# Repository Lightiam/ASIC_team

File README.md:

# ASIC_team

Consolidating codes

This repository is intended to hold consolidated code and resources for the ASIC team.

## Authors & Contributors

- ** RTL and Digital Designer:** Talha Alam
- ** Architect, Co-Designer:** Founder, CEO-  Bola Olatunji

## Getting started

- Clone the repository: `git clone git@github.com:Lightiam/ASIC_team.git`
- Create a branch for your work: `git checkout -b feat/your-feature`
- Commit and open a pull request against `main`.

## Contributing

Please follow a lightweight workflow:
- Use feature branches (branch names like `feat/...`, `fix/...`, `chore/...`).
- Open pull requests and request a review.
- Keep commits small and descriptive.

## License

This repository is released under CC0 1.0 Universal. See the LICENSE file.

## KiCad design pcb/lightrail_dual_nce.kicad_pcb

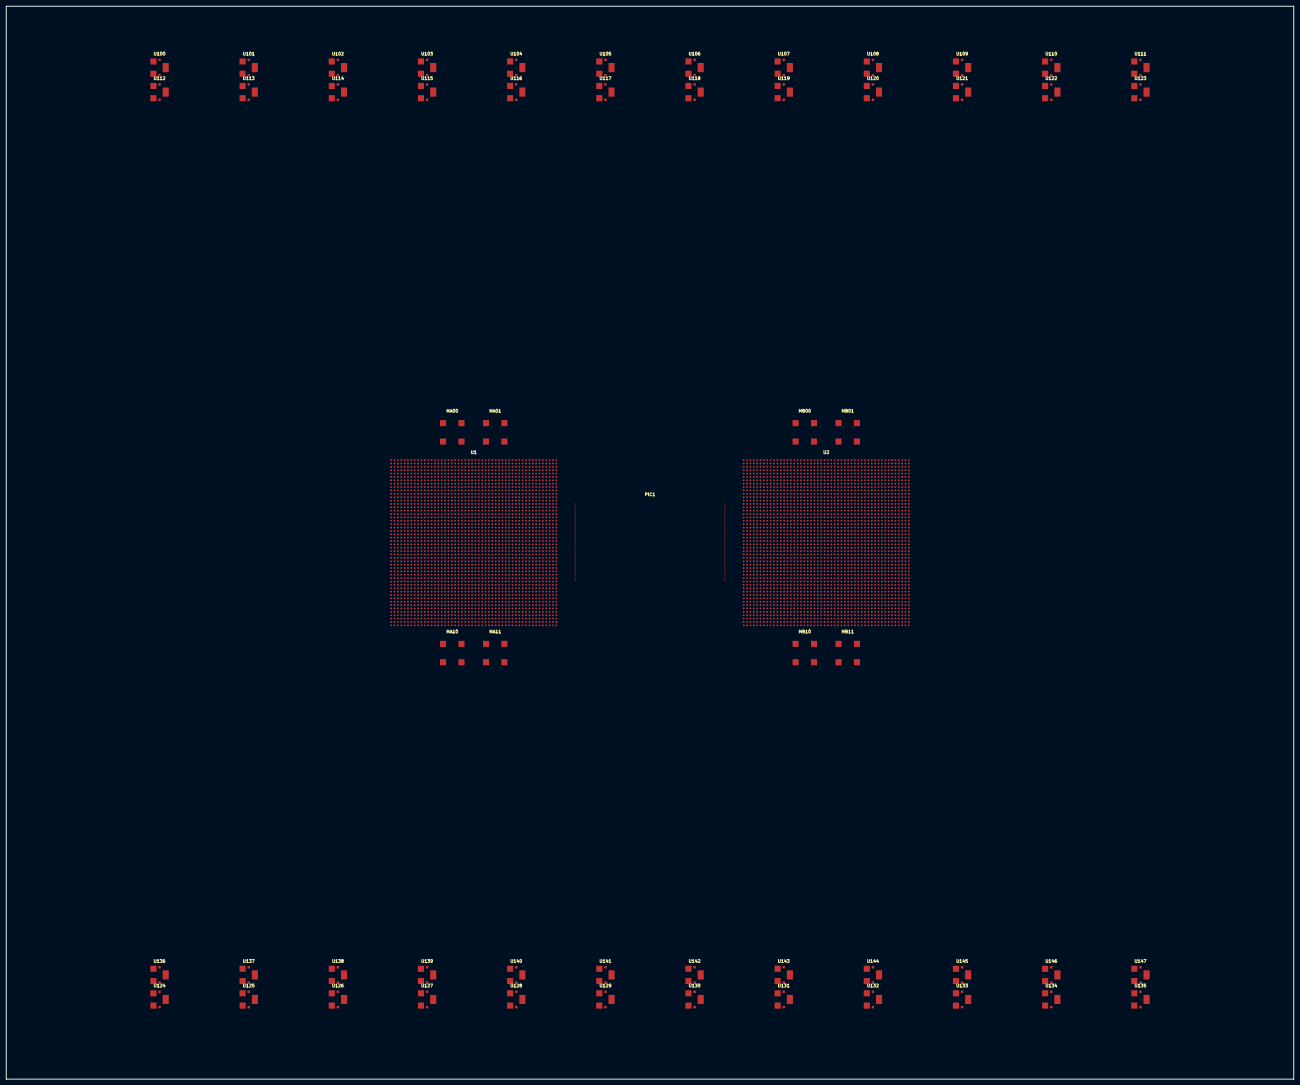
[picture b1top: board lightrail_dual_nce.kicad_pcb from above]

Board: 32 copper layers, 420.0 x 350.0 mm, 59 parts (0 on the bottom side), 131 nets, no tracks yet.

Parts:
MA00, MA01, MA10, MA11: HBM4-12Hi
MB00, MB01, MB10, MB11: HBM4-12Hi
PIC1: TFLN-BRIDGE-3T2
U1, U2: NCE-BGA2500
U100, U101, U102, U103, U104, U105, U106, U107, U108, U109, U110, U111, U112, U113, U114, U115, U116, U117, U118, U119, U120, U121, U122, U123, U124, U125, U126, U127, U128, U129, U130, U131, U132, U133, U134, U135, U136, U137, U138, U139, U140, U141, U142, U143, U144, U145, U146, U147: DrMOS

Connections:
GND: MA00.GND, MA00.VSSQ, MA01.GND, MA01.VSSQ, MA10.GND, MA10.VSSQ, MA11.GND, MA11.VSSQ, MB00.GND, MB00.VSSQ, MB01.GND, MB01.VSSQ, MB10.GND, MB10.VSSQ, MB11.GND, MB11.VSSQ, U1.AA4, U1.AA6, U1.AA8, U1.AA10, U1.AA12, U1.AA14, U1.AA16, U1.AA18, U1.AA20, U1.AA22, U1.AA24, U1.AA26, U1.AA28, U1.AA30, U1.AA32, U1.AA34, U1.AA36, U1.AA38, U1.AA40, U1.AA42, U1.AA44, U1.AA46, U1.AB3, U1.AB5, U1.AB7, U1.AB9, U1.AB11, U1.AB13, U1.AB15, U1.AB17, U1.AB19, U1.AB21, U1.AB23, U1.AB25, U1.AB27, U1.AB29, U1.AB31, U1.AB33, U1.AB35, U1.AB37, U1.AB39, U1.AB41, U1.AB43, U1.AB45, U1.AB47, U1.AC4, U1.AC6, U1.AC8, U1.AC10, U1.AC12, U1.AC14, U1.AC16, U1.AC18, U1.AC20, U1.AC22, U1.AC24, U1.AC26, U1.AC28, U1.AC30, U1.AC32, U1.AC34, U1.AC36, U1.AC38, U1.AC40, U1.AC42, U1.AC44, U1.AC46, U1.AD3, U1.AD5, U1.AD7, U1.AD9, U1.AD11, U1.AD13, U1.AD15, U1.AD17, U1.AD19, U1.AD21, U1.AD23, U1.AD25, U1.AD27, U1.AD29, U1.AD31, U1.AD33, U1.AD35, U1.AD37, U1.AD39, U1.AD41, U1.AD43, U1.AD45, U1.AD47, U1.AE4, U1.AE6, U1.AE8, U1.AE10, U1.AE12, U1.AE14, U1.AE16, U1.AE18, U1.AE20, U1.AE22, U1.AE24, U1.AE26, U1.AE28, U1.AE30, U1.AE32, U1.AE34, U1.AE36, U1.AE38, U1.AE40, U1.AE42, U1.AE44, U1.AE46, U1.AF3, U1.AF5, U1.AF7, U1.AF9, U1.AF11, U1.AF13, U1.AF15, U1.AF17, U1.AF19, U1.AF21, U1.AF23, U1.AF25, U1.AF27, U1.AF29, U1.AF31, U1.AF33, U1.AF35, U1.AF37, U1.AF39, U1.AF41, U1.AF43, U1.AF45, U1.AF47, U1.AG4, U1.AG6, U1.AG8, U1.AG10, U1.AG12, U1.AG14, U1.AG16, U1.AG18, U1.AG20, U1.AG22, U1.AG24, U1.AG26, U1.AG28, U1.AG30, U1.AG32, U1.AG34, U1.AG36, U1.AG38, U1.AG40, U1.AG42, U1.AG44, U1.AG46, U1.AH3, U1.AH5, U1.AH7, U1.AH9, U1.AH11, U1.AH13, U1.AH15, U1.AH17, U1.AH19, U1.AH21, U1.AH23, U1.AH25, U1.AH27, U1.AH29, U1.AH31, U1.AH33, U1.AH35, U1.AH37, U1.AH39, U1.AH41, U1.AH43, U1.AH45, U1.AH47, U1.AJ4, U1.AJ6, U1.AJ8, U1.AJ10, U1.AJ12, U1.AJ14, U1.AJ16, U1.AJ18, U1.AJ20, U1.AJ22, U1.AJ24, U1.AJ26, U1.AJ28, U1.AJ30, U1.AJ32, U1.AJ34, U1.AJ36, U1.AJ38, U1.AJ40, U1.AJ42, U1.AJ44, U1.AJ46, U1.AK3, U1.AK5, U1.AK7, U1.AK9, U1.AK11, U1.AK13, U1.AK15, U1.AK17, U1.AK19, U1.AK21, U1.AK23, U1.AK25, U1.AK27, U1.AK29, U1.AK31, U1.AK33, U1.AK35, U1.AK37, U1.AK39, U1.AK41, U1.AK43, U1.AK45, U1.AK47, U1.AL4, U1.AL6, U1.AL8, U1.AL10, U1.AL12, U1.AL14, U1.AL16, U1.AL18, U1.AL20, U1.AL22, U1.AL24, U1.AL26, U1.AL28, U1.AL30, U1.AL32, U1.AL34, U1.AL36, U1.AL38, U1.AL40, U1.AL42, U1.AL44, U1.AL46, U1.AM3, U1.AM5, U1.AM7, U1.AM9, U1.AM11, U1.AM13, U1.AM15, U1.AM17, U1.AM19, U1.AM21, U1.AM23, U1.AM25, U1.AM27, U1.AM29, U1.AM31, U1.AM33, U1.AM35, U1.AM37, U1.AM39, U1.AM41, U1.AM43, U1.AM45, U1.AM47, U1.AN4, U1.AN6, U1.AN8, U1.AN10, U1.AN12, U1.AN14, U1.AN16, U1.AN18, U1.AN20, U1.AN22, U1.AN24, U1.AN26, U1.AN28, U1.AN30, U1.AN32, U1.AN34, U1.AN36, U1.AN38, U1.AN40, U1.AN42, U1.AN44, U1.AN46, U1.AP3, U1.AP5, U1.AP7, U1.AP9, U1.AP11, U1.AP13, U1.AP15, U1.AP17, U1.AP19, U1.AP21, U1.AP23, U1.AP25, U1.AP27, U1.AP29, U1.AP31, U1.AP33, U1.AP35, U1.AP37, U1.AP39, U1.AP41, U1.AP43, U1.AP45, U1.AP47, U1.AR4, U1.AR6, U1.AR8, U1.AR10, U1.AR12, U1.AR14, U1.AR16, U1.AR18, U1.AR20, U1.AR22, U1.AR24, U1.AR26, U1.AR28, U1.AR30, U1.AR32, U1.AR34, U1.AR36, U1.AR38, U1.AR40, U1.AR42, U1.AR44, U1.AR46, U1.AT3, U1.AT5, U1.AT7, U1.AT9, U1.AT11, U1.AT13, U1.AT15, U1.AT17, U1.AT19, U1.AT21, U1.AT23, U1.AT25, U1.AT27, U1.AT29, U1.AT31, U1.AT33, U1.AT35, U1.AT37, U1.AT39, U1.AT41, U1.AT43, U1.AT45, U1.AT47, U1.AU4, U1.AU6, U1.AU8, U1.AU10, U1.AU12, U1.AU14, U1.AU16, U1.AU18, U1.AU20, U1.AU22, U1.AU24, U1.AU26, U1.AU28, U1.AU30, U1.AU32, U1.AU34, U1.AU36, U1.AU38, U1.AU40, U1.AU42, U1.AU44, U1.AU46, U1.AU48, U1.AV3, U1.AV5, U1.AV7, U1.AV9, U1.AV11, U1.AV13, U1.AV15, U1.AV17, U1.AV19, U1.AV21, U1.AV23, U1.AV25, U1.AV27, U1.AV29, U1.AV31, U1.AV33, U1.AV35, U1.AV37, U1.AV39, U1.AV41, U1.AV43, U1.AV45, U1.AV47, U1.AW4, U1.AW6, U1.AW8, U1.AW10, U1.AW12, U1.AW14, U1.AW16, U1.AW18, U1.AW20, U1.AW22, U1.AW24, U1.AW26, U1.AW28, U1.AW30, U1.AW32, U1.AW34, U1.AW36, U1.AW38, U1.AW40, U1.AW42, U1.AW44, U1.AW46, U1.AW48, U1.AY3, U1.AY5, U1.AY7, U1.AY9, U1.AY11, U1.AY13, U1.AY15, U1.AY17, U1.AY19, U1.AY21, U1.AY23, U1.AY25, U1.AY27, U1.AY29, U1.AY31, U1.AY33, U1.AY35, U1.AY37, U1.AY39, U1.AY41, U1.AY43, U1.AY45, U1.AY47, U1.BA4, U1.BA6, U1.BA8, U1.BA10, U1.BA12, U1.BA14, U1.BA16, U1.BA18, U1.BA20, U1.BA22, U1.BA24, U1.BA26, U1.BA28, U1.BA30, U1.BA32, U1.BA34, U1.BA36, U1.BA38, U1.BA40, U1.BA42, U1.BA44, U1.BA46, U1.BA48, U1.BB3, U1.BB5, U1.BB7, U1.BB9, U1.BB11, U1.BB13, U1.BB15, U1.BB17, U1.BB19, U1.BB21, U1.BB23, U1.BB25, U1.BB27, U1.BB29, U1.BB31, U1.BB33, U1.BB35, U1.BB37, U1.BB39, U1.BB41, U1.BB43, U1.BB45, U1.BB47, U1.BC4, U1.BC6, U1.BC8, U1.BC10, U1.BC12, U1.BC14, U1.BC16, U1.BC18, U1.BC20, U1.BC22, U1.BC24, U1.BC26, U1.BC28, U1.BC30, U1.BC32, U1.BC34, U1.BC36, U1.BC38, U1.BC40, U1.BC42, U1.BC44, U1.BC46, U1.BC48, U1.BD3, U1.BD5, U1.BD7, U1.BD9, U1.BD11, U1.BD13, U1.BD15, U1.BD17, U1.BD19, U1.BD21, U1.BD23, U1.BD25, U1.BD27, U1.BD29, U1.BD31, U1.BD33, U1.BD35, U1.BD37, U1.BD39, U1.BD41, U1.BD43, U1.BD45, U1.BD47, U1.BE4, U1.BE6, U1.BE8, U1.BE10, U1.BE12, U1.BE14, U1.BE16, U1.BE18, U1.BE20, U1.BE22, U1.BE24, U1.BE26, U1.BE28, U1.BE30, U1.BE32, U1.BE34, U1.BE36, U1.BE38, U1.BE40, U1.BE42, U1.BE44, U1.BE46, U1.BE48, U1.BF3, U1.BF5, U1.BF7, U1.BF9, U1.BF11, U1.BF13, U1.BF15, U1.BF17, U1.BF19, U1.BF21, U1.BF23, U1.BF25, U1.BF27, U1.BF29, U1.BF31, U1.BF33, U1.BF35, U1.BF37, U1.BF39, U1.BF41, U1.BF43, U1.BF45, U1.BF47, U1.BG4, U1.BG6, U1.BG8, U1.BG10, U1.BG12, U1.BG14, U1.BG16, U1.BG18, U1.BG20, U1.BG22, U1.BG24, U1.BG26, U1.BG28, U1.BG30, U1.BG32, U1.BG34, U1.BG36, U1.BG38, U1.BG40, U1.BG42, U1.BG44, U1.BG46, U1.BG48, U1.BH3, U1.BH5, U1.BH7, U1.BH9, U1.BH11, U1.BH13, U1.BH15, U1.BH17, U1.BH19, U1.BH21, U1.BH23, U1.BH25, U1.BH27, U1.BH29, U1.BH31, U1.BH33, U1.BH35, U1.BH37, U1.BH39, U1.BH41, U1.BH43, U1.BH45, U1.BH47, U1.C4, U1.C6, U1.C8, U1.C10, U1.C12, U1.C14, U1.C16, U1.C18, U1.C20, U1.C22, U1.C24, U1.C26, U1.C28, U1.C30, U1.C32, U1.C34, U1.C36, U1.C38, U1.C40, U1.C42, U1.C44, U1.C46, U1.C48, U1.D3, U1.D5, U1.D7, U1.D9, U1.D11, U1.D13, U1.D15, U1.D17, U1.D19, U1.D21, U1.D23, U1.D25, U1.D27, U1.D29, U1.D31, U1.D33, U1.D35, U1.D37, U1.D39, U1.D41, U1.D43, U1.D45, U1.D47, U1.E4, U1.E6, U1.E8, U1.E10, U1.E12, U1.E14, U1.E16, U1.E18, U1.E20, U1.E22, U1.E24, U1.E26, U1.E28, U1.E30, U1.E32, U1.E34, U1.E36, U1.E38, U1.E40, U1.E42, U1.E44, U1.E46, U1.F3, U1.F5, U1.F7, U1.F9, U1.F11, U1.F13, U1.F15, U1.F17, U1.F19, U1.F21, U1.F23, U1.F25, U1.F27, U1.F29, U1.F31, U1.F33, U1.F35, U1.F37, U1.F39, U1.F41, U1.F43, U1.F45, U1.F47, U1.G4, U1.G6, U1.G8, U1.G10, U1.G12, U1.G14, U1.G16, U1.G18, U1.G20, U1.G22, U1.G24, U1.G26, U1.G28, U1.G30, U1.G32, U1.G34, U1.G36, U1.G38, U1.G40, U1.G42, U1.G44, U1.G46, U1.H3, U1.H5, U1.H7, U1.H9, U1.H11, U1.H13, U1.H15, U1.H17, U1.H19, U1.H21, U1.H23, U1.H25, U1.H27, U1.H29, U1.H31, U1.H33, U1.H35, U1.H37, U1.H39, U1.H41, U1.H43, U1.H45, U1.H47, U1.J4, U1.J6, U1.J8, U1.J10, U1.J12, U1.J14, U1.J16, U1.J18, U1.J20, U1.J22, U1.J24, U1.J26, U1.J28, U1.J30, U1.J32, U1.J34, U1.J36, U1.J38, U1.J40, U1.J42, U1.J44, U1.J46, U1.K3, U1.K5, U1.K7, U1.K9, U1.K11, U1.K13, U1.K15, U1.K17, U1.K19, U1.K21, U1.K23, U1.K25, U1.K27, U1.K29, U1.K31, U1.K33, U1.K35, U1.K37, U1.K39, U1.K41, U1.K43, U1.K45, U1.K47, U1.L4, U1.L6, U1.L8, U1.L10, U1.L12, U1.L14, U1.L16, U1.L18, U1.L20, U1.L22, U1.L24, U1.L26, U1.L28, U1.L30, U1.L32, U1.L34, U1.L36, U1.L38, U1.L40, U1.L42, U1.L44, U1.L46, U1.M3, U1.M5, U1.M7, U1.M9, U1.M11, U1.M13, U1.M15, U1.M17, U1.M19, U1.M21, U1.M23, U1.M25, U1.M27, U1.M29, U1.M31, U1.M33, U1.M35, U1.M37, U1.M39, U1.M41, U1.M43, U1.M45, U1.M47, U1.N4, U1.N6, U1.N8, U1.N10, U1.N12, U1.N14, U1.N16, U1.N18, U1.N20, U1.N22, U1.N24, U1.N26, U1.N28, U1.N30, U1.N32, U1.N34, U1.N36, U1.N38, U1.N40, U1.N42, U1.N44, U1.N46, U1.P3, U1.P5, U1.P7, U1.P9, U1.P11, U1.P13, U1.P15, U1.P17, U1.P19, U1.P21, U1.P23, U1.P25, U1.P27, U1.P29, U1.P31, U1.P33, U1.P35, U1.P37, U1.P39, U1.P41, U1.P43, U1.P45, U1.P47, U1.R4, U1.R6, U1.R8, U1.R10, U1.R12, U1.R14, U1.R16, U1.R18, U1.R20, U1.R22, U1.R24, U1.R26, U1.R28, U1.R30, U1.R32, U1.R34, U1.R36, U1.R38, U1.R40, U1.R42, U1.R44, U1.R46, U1.T3, U1.T5, U1.T7, U1.T9, U1.T11, U1.T13, U1.T15, U1.T17, U1.T19, U1.T21, U1.T23, U1.T25, U1.T27, U1.T29, U1.T31, U1.T33, U1.T35, U1.T37, U1.T39, U1.T41, U1.T43, U1.T45, U1.T47, U1.U4, U1.U6, U1.U8, U1.U10, U1.U12, U1.U14, U1.U16, U1.U18, U1.U20, U1.U22, U1.U24, U1.U26, U1.U28, U1.U30, U1.U32, U1.U34, U1.U36, U1.U38, U1.U40, U1.U42, U1.U44, U1.U46, U1.V3, U1.V5, U1.V7, U1.V9, U1.V11, U1.V13, U1.V15, U1.V17, U1.V19, U1.V21, U1.V23, U1.V25, U1.V27, U1.V29, U1.V31, U1.V33, U1.V35, U1.V37, U1.V39, U1.V41, U1.V43, U1.V45, U1.V47, U1.W4, U1.W6, U1.W8, U1.W10, U1.W12, U1.W14, U1.W16, U1.W18, U1.W20, U1.W22, U1.W24, U1.W26, U1.W28, U1.W30, U1.W32, U1.W34, U1.W36, U1.W38, U1.W40, U1.W42, U1.W44, U1.W46, U1.Y3, U1.Y5, U1.Y7, U1.Y9, U1.Y11, U1.Y13, U1.Y15, U1.Y17, U1.Y19, U1.Y21, U1.Y23, U1.Y25, U1.Y27, U1.Y29, U1.Y31, U1.Y33, U1.Y35, U1.Y37, U1.Y39, U1.Y41, U1.Y43, U1.Y45, U1.Y47, U2.AA4, U2.AA6, U2.AA8, U2.AA10, U2.AA12, U2.AA14, U2.AA16, U2.AA18, U2.AA20, U2.AA22, U2.AA24, U2.AA26, U2.AA28, U2.AA30, U2.AA32, U2.AA34, U2.AA36, U2.AA38, U2.AA40, U2.AA42, U2.AA44, U2.AA46, U2.AA48, U2.AB5, U2.AB7, U2.AB9, U2.AB11, U2.AB13, U2.AB15, U2.AB17, U2.AB19, U2.AB21, U2.AB23, U2.AB25, U2.AB27, U2.AB29, U2.AB31, U2.AB33, U2.AB35, U2.AB37, U2.AB39, U2.AB41, U2.AB43, U2.AB45, U2.AB47, U2.AC4, U2.AC6, U2.AC8, U2.AC10, U2.AC12, U2.AC14, U2.AC16, U2.AC18, U2.AC20, U2.AC22, U2.AC24, U2.AC26, U2.AC28, U2.AC30, U2.AC32, U2.AC34, U2.AC36, U2.AC38, U2.AC40, U2.AC42, U2.AC44, U2.AC46, U2.AC48, U2.AD5, U2.AD7, U2.AD9, U2.AD11, U2.AD13, U2.AD15, U2.AD17, U2.AD19, U2.AD21, U2.AD23, U2.AD25, U2.AD27, U2.AD29, U2.AD31, U2.AD33, U2.AD35, U2.AD37, U2.AD39, U2.AD41, U2.AD43, U2.AD45, U2.AD47, U2.AE4, U2.AE6, U2.AE8, U2.AE10, U2.AE12, U2.AE14, U2.AE16, U2.AE18, U2.AE20, U2.AE22, U2.AE24, U2.AE26, U2.AE28, U2.AE30, U2.AE32, U2.AE34, U2.AE36, U2.AE38, U2.AE40, U2.AE42, U2.AE44, U2.AE46, U2.AE48, U2.AF5, U2.AF7, U2.AF9, U2.AF11, U2.AF13, U2.AF15, U2.AF17, U2.AF19, U2.AF21, U2.AF23, U2.AF25, U2.AF27, U2.AF29, U2.AF31, U2.AF33, U2.AF35, U2.AF37, U2.AF39, U2.AF41, U2.AF43, U2.AF45, U2.AF47, U2.AG4, U2.AG6, U2.AG8, U2.AG10, U2.AG12, U2.AG14, U2.AG16, U2.AG18, U2.AG20, U2.AG22, U2.AG24, U2.AG26, U2.AG28, U2.AG30, U2.AG32, U2.AG34, U2.AG36, U2.AG38, U2.AG40, U2.AG42, U2.AG44, U2.AG46, U2.AG48, U2.AH5, U2.AH7, U2.AH9, U2.AH11, U2.AH13, U2.AH15, U2.AH17, U2.AH19, U2.AH21, U2.AH23, U2.AH25, U2.AH27, U2.AH29, U2.AH31, U2.AH33, U2.AH35, U2.AH37, U2.AH39, U2.AH41, U2.AH43, U2.AH45, U2.AH47, U2.AJ4, U2.AJ6, U2.AJ8, U2.AJ10, U2.AJ12, U2.AJ14, U2.AJ16, U2.AJ18, U2.AJ20, U2.AJ22, U2.AJ24, U2.AJ26, U2.AJ28, U2.AJ30, U2.AJ32, U2.AJ34, U2.AJ36, U2.AJ38, U2.AJ40, U2.AJ42, U2.AJ44, U2.AJ46, U2.AJ48, U2.AK5, U2.AK7, U2.AK9, U2.AK11, U2.AK13, U2.AK15, U2.AK17, U2.AK19, U2.AK21, U2.AK23, U2.AK25, U2.AK27, U2.AK29, U2.AK31, U2.AK33, U2.AK35, U2.AK37, U2.AK39, U2.AK41, U2.AK43, U2.AK45, U2.AK47, U2.AL4, U2.AL6, U2.AL8, U2.AL10, U2.AL12, U2.AL14, U2.AL16, U2.AL18, U2.AL20, U2.AL22, U2.AL24, U2.AL26, U2.AL28, U2.AL30, U2.AL32, U2.AL34, U2.AL36, U2.AL38, U2.AL40, U2.AL42, U2.AL44, U2.AL46, U2.AL48, U2.AM5, U2.AM7, U2.AM9, U2.AM11, U2.AM13, U2.AM15, U2.AM17, U2.AM19, U2.AM21, U2.AM23, U2.AM25, U2.AM27, U2.AM29, U2.AM31, U2.AM33, U2.AM35, U2.AM37, U2.AM39, U2.AM41, U2.AM43, U2.AM45, U2.AM47, U2.AN4, U2.AN6, U2.AN8, U2.AN10, U2.AN12, U2.AN14, U2.AN16, U2.AN18, U2.AN20, U2.AN22, U2.AN24, U2.AN26, U2.AN28, U2.AN30, U2.AN32, U2.AN34, U2.AN36, U2.AN38, U2.AN40, U2.AN42, U2.AN44, U2.AN46, U2.AN48, U2.AP5, U2.AP7, U2.AP9, U2.AP11, U2.AP13, U2.AP15, U2.AP17, U2.AP19, U2.AP21, U2.AP23, U2.AP25, U2.AP27, U2.AP29, U2.AP31, U2.AP33, U2.AP35, U2.AP37, U2.AP39, U2.AP41, U2.AP43, U2.AP45, U2.AP47, U2.AR4, U2.AR6, U2.AR8, U2.AR10, U2.AR12, U2.AR14, U2.AR16, U2.AR18, U2.AR20, U2.AR22, U2.AR24, U2.AR26, U2.AR28, U2.AR30, U2.AR32, U2.AR34, U2.AR36, U2.AR38, U2.AR40, U2.AR42, U2.AR44, U2.AR46, U2.AR48, U2.AT5, U2.AT7, U2.AT9, U2.AT11, U2.AT13, U2.AT15, U2.AT17, U2.AT19, U2.AT21, U2.AT23, U2.AT25, U2.AT27, U2.AT29, U2.AT31, U2.AT33, U2.AT35, U2.AT37, U2.AT39, U2.AT41, U2.AT43, U2.AT45, U2.AT47, U2.AU4, U2.AU6, U2.AU8, U2.AU10, U2.AU12, U2.AU14, U2.AU16, U2.AU18, U2.AU20, U2.AU22, U2.AU24, U2.AU26, U2.AU28, U2.AU30, U2.AU32, U2.AU34, U2.AU36, U2.AU38, U2.AU40, U2.AU42, U2.AU44, U2.AU46, U2.AU48, U2.AV3, U2.AV5, U2.AV7, U2.AV9, U2.AV11, U2.AV13, U2.AV15, U2.AV17, U2.AV19, U2.AV21, U2.AV23, U2.AV25, U2.AV27, U2.AV29, U2.AV31, U2.AV33, U2.AV35, U2.AV37, U2.AV39, U2.AV41, U2.AV43, U2.AV45, U2.AV47, U2.AW4, U2.AW6, U2.AW8, U2.AW10, U2.AW12, U2.AW14, U2.AW16, U2.AW18, U2.AW20, U2.AW22, U2.AW24, U2.AW26, U2.AW28, U2.AW30, U2.AW32, U2.AW34, U2.AW36, U2.AW38, U2.AW40, U2.AW42, U2.AW44, U2.AW46, U2.AW48, U2.AY3, U2.AY5, U2.AY7, U2.AY9, U2.AY11, U2.AY13, U2.AY15, U2.AY17, U2.AY19, U2.AY21, U2.AY23, U2.AY25, U2.AY27, U2.AY29, U2.AY31, U2.AY33, U2.AY35, U2.AY37, U2.AY39, U2.AY41, U2.AY43, U2.AY45, U2.AY47, U2.BA4, U2.BA6, U2.BA8, U2.BA10, U2.BA12, U2.BA14, U2.BA16, U2.BA18, U2.BA20, U2.BA22, U2.BA24, U2.BA26, U2.BA28, U2.BA30, U2.BA32, U2.BA34, U2.BA36, U2.BA38, U2.BA40, U2.BA42, U2.BA44, U2.BA46, U2.BA48, U2.BB3, U2.BB5, U2.BB7, U2.BB9, U2.BB11, U2.BB13, U2.BB15, U2.BB17, U2.BB19, U2.BB21, U2.BB23, U2.BB25, U2.BB27, U2.BB29, U2.BB31, U2.BB33, U2.BB35, U2.BB37, U2.BB39, U2.BB41, U2.BB43, U2.BB45, U2.BB47, U2.BC4, U2.BC6, U2.BC8, U2.BC10, U2.BC12, U2.BC14, U2.BC16, U2.BC18, U2.BC20, U2.BC22, U2.BC24, U2.BC26, U2.BC28, U2.BC30, U2.BC32, U2.BC34, U2.BC36, U2.BC38, U2.BC40, U2.BC42, U2.BC44, U2.BC46, U2.BC48, U2.BD3, U2.BD5, U2.BD7, U2.BD9, U2.BD11, U2.BD13, U2.BD15, U2.BD17, U2.BD19, U2.BD21, U2.BD23, U2.BD25, U2.BD27, U2.BD29, U2.BD31, U2.BD33, U2.BD35, U2.BD37, U2.BD39, U2.BD41, U2.BD43, U2.BD45, U2.BD47, U2.BE4, U2.BE6, U2.BE8, U2.BE10, U2.BE12, U2.BE14, U2.BE16, U2.BE18, U2.BE20, U2.BE22, U2.BE24, U2.BE26, U2.BE28, U2.BE30, U2.BE32, U2.BE34, U2.BE36, U2.BE38, U2.BE40, U2.BE42, U2.BE44, U2.BE46, U2.BE48, U2.BF3, U2.BF5, U2.BF7, U2.BF9, U2.BF11, U2.BF13, U2.BF15, U2.BF17, U2.BF19, U2.BF21, U2.BF23, U2.BF25, U2.BF27, U2.BF29, U2.BF31, U2.BF33, U2.BF35, U2.BF37, U2.BF39, U2.BF41, U2.BF43, U2.BF45, U2.BF47, U2.BG4, U2.BG6, U2.BG8, U2.BG10, U2.BG12, U2.BG14, U2.BG16, U2.BG18, U2.BG20, U2.BG22, U2.BG24, U2.BG26, U2.BG28, U2.BG30, U2.BG32, U2.BG34, U2.BG36, U2.BG38, U2.BG40, U2.BG42, U2.BG44, U2.BG46, U2.BG48, U2.BH3, U2.BH5, U2.BH7, U2.BH9, U2.BH11, U2.BH13, U2.BH15, U2.BH17, U2.BH19, U2.BH21, U2.BH23, U2.BH25, U2.BH27, U2.BH29, U2.BH31, U2.BH33, U2.BH35, U2.BH37, U2.BH39, U2.BH41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
U1_RX0_N: PIC1.U1_TX0N, U1.AA49
U1_RX0_P: PIC1.U1_TX0P, U1.AA48
U1_RX1_N: PIC1.U1_TX1N, U1.AB49
U1_RX1_P: PIC1.U1_TX1P, U1.AB48
U1_RX2_N: PIC1.U1_TX2N, U1.AC49
U1_RX2_P: PIC1.U1_TX2P, U1.AC48
U1_RX3_N: PIC1.U1_TX3N, U1.AD49
U1_RX3_P: PIC1.U1_TX3P, U1.AD48
U1_RX4_N: PIC1.U1_TX4N, U1.AE49
U1_RX4_P: PIC1.U1_TX4P, U1.AE48
U1_RX5_N: PIC1.U1_TX5N, U1.AF49
U1_RX5_P: PIC1.U1_TX5P, U1.AF48
U1_RX6_N: PIC1.U1_TX6N, U1.AG49
U1_RX6_P: PIC1.U1_TX6P, U1.AG48
U1_RX7_N: PIC1.U1_TX7N, U1.AH49
U1_RX7_P: PIC1.U1_TX7P, U1.AH48
U1_RX8_N: PIC1.U1_TX8N, U1.AJ49
U1_RX8_P: PIC1.U1_TX8P, U1.AJ48
U1_RX9_N: PIC1.U1_TX9N, U1.AK49
U1_RX9_P: PIC1.U1_TX9P, U1.AK48
U1_RX10_N: PIC1.U1_TX10N, U1.AL49
U1_RX10_P: PIC1.U1_TX10P, U1.AL48
U1_RX11_N: PIC1.U1_TX11N, U1.AM49
U1_RX11_P: PIC1.U1_TX11P, U1.AM48
U1_RX12_N: PIC1.U1_TX12N, U1.AN49
U1_RX12_P: PIC1.U1_TX12P, U1.AN48
U1_RX13_N: PIC1.U1_TX13N, U1.AP49
U1_RX13_P: PIC1.U1_TX13P, U1.AP48
U1_RX14_N: PIC1.U1_TX14N, U1.AR49
U1_RX14_P: PIC1.U1_TX14P, U1.AR48
U1_RX15_N: PIC1.U1_TX15N, U1.AT49
U1_RX15_P: PIC1.U1_TX15P, U1.AT48
U1_TX0_N: PIC1.U1_RX0N, U1.E49
U1_TX0_P: PIC1.U1_RX0P, U1.E48
U1_TX1_N: PIC1.U1_RX1N, U1.F49
U1_TX1_P: PIC1.U1_RX1P, U1.F48
U1_TX2_N: PIC1.U1_RX2N, U1.G49
U1_TX2_P: PIC1.U1_RX2P, U1.G48
U1_TX3_N: PIC1.U1_RX3N, U1.H49
U1_TX3_P: PIC1.U1_RX3P, U1.H48
U1_TX4_N: PIC1.U1_RX4N, U1.J49
U1_TX4_P: PIC1.U1_RX4P, U1.J48
U1_TX5_N: PIC1.U1_RX5N, U1.K49
U1_TX5_P: PIC1.U1_RX5P, U1.K48
U1_TX6_N: PIC1.U1_RX6N, U1.L49
U1_TX6_P: PIC1.U1_RX6P, U1.L48
U1_TX7_N: PIC1.U1_RX7N, U1.M49
U1_TX7_P: PIC1.U1_RX7P, U1.M48
U1_TX8_N: PIC1.U1_RX8N, U1.N49
U1_TX8_P: PIC1.U1_RX8P, U1.N48
U1_TX9_N: PIC1.U1_RX9N, U1.P49
U1_TX9_P: PIC1.U1_RX9P, U1.P48
U1_TX10_N: PIC1.U1_RX10N, U1.R49
U1_TX10_P: PIC1.U1_RX10P, U1.R48
U1_TX11_N: PIC1.U1_RX11N, U1.T49
U1_TX11_P: PIC1.U1_RX11P, U1.T48
U1_TX12_N: PIC1.U1_RX12N, U1.U49
U1_TX12_P: PIC1.U1_RX12P, U1.U48
U1_TX13_N: PIC1.U1_RX13N, U1.V49
U1_TX13_P: PIC1.U1_RX13P, U1.V48
U1_TX14_N: PIC1.U1_RX14N, U1.W49
U1_TX14_P: PIC1.U1_RX14P, U1.W48
U1_TX15_N: PIC1.U1_RX15N, U1.Y49
U1_TX15_P: PIC1.U1_RX15P, U1.Y48
U2_RX0_N: PIC1.U2_TX0N, U2.AA3
U2_RX0_P: PIC1.U2_TX0P, U2.AA2
U2_RX1_N: PIC1.U2_TX1N, U2.AB3
U2_RX1_P: PIC1.U2_TX1P, U2.AB2
U2_RX2_N: PIC1.U2_TX2N, U2.AC3
U2_RX2_P: PIC1.U2_TX2P, U2.AC2
U2_RX3_N: PIC1.U2_TX3N, U2.AD3
U2_RX3_P: PIC1.U2_TX3P, U2.AD2
U2_RX4_N: PIC1.U2_TX4N, U2.AE3
U2_RX4_P: PIC1.U2_TX4P, U2.AE2
U2_RX5_N: PIC1.U2_TX5N, U2.AF3
U2_RX5_P: PIC1.U2_TX5P, U2.AF2
U2_RX6_N: PIC1.U2_TX6N, U2.AG3
U2_RX6_P: PIC1.U2_TX6P, U2.AG2
U2_RX7_N: PIC1.U2_TX7N, U2.AH3
U2_RX7_P: PIC1.U2_TX7P, U2.AH2
U2_RX8_N: PIC1.U2_TX8N, U2.AJ3
U2_RX8_P: PIC1.U2_TX8P, U2.AJ2
U2_RX9_N: PIC1.U2_TX9N, U2.AK3
U2_RX9_P: PIC1.U2_TX9P, U2.AK2
U2_RX10_N: PIC1.U2_TX10N, U2.AL3
U2_RX10_P: PIC1.U2_TX10P, U2.AL2
U2_RX11_N: PIC1.U2_TX11N, U2.AM3
U2_RX11_P: PIC1.U2_TX11P, U2.AM2
U2_RX12_N: PIC1.U2_TX12N, U2.AN3
U2_RX12_P: PIC1.U2_TX12P, U2.AN2
U2_RX13_N: PIC1.U2_TX13N, U2.AP3
U2_RX13_P: PIC1.U2_TX13P, U2.AP2
U2_RX14_N: PIC1.U2_TX14N, U2.AR3
U2_RX14_P: PIC1.U2_TX14P, U2.AR2
U2_RX15_N: PIC1.U2_TX15N, U2.AT3
U2_RX15_P: PIC1.U2_TX15P, U2.AT2
U2_TX0_N: PIC1.U2_RX0N, U2.E3
U2_TX0_P: PIC1.U2_RX0P, U2.E2
U2_TX1_N: PIC1.U2_RX1N, U2.F3
U2_TX1_P: PIC1.U2_RX1P, U2.F2
U2_TX2_N: PIC1.U2_RX2N, U2.G3
U2_TX2_P: PIC1.U2_RX2P, U2.G2
U2_TX3_N: PIC1.U2_RX3N, U2.H3
U2_TX3_P: PIC1.U2_RX3P, U2.H2
U2_TX4_N: PIC1.U2_RX4N, U2.J3
U2_TX4_P: PIC1.U2_RX4P, U2.J2
U2_TX5_N: PIC1.U2_RX5N, U2.K3
U2_TX5_P: PIC1.U2_RX5P, U2.K2
U2_TX6_N: PIC1.U2_RX6N, U2.L3
U2_TX6_P: PIC1.U2_RX6P, U2.L2
U2_TX7_N: PIC1.U2_RX7N, U2.M3
U2_TX7_P: PIC1.U2_RX7P, U2.M2
U2_TX8_N: PIC1.U2_RX8N, U2.N3
U2_TX8_P: PIC1.U2_RX8P, U2.N2
U2_TX9_N: PIC1.U2_RX9N, U2.P3
U2_TX9_P: PIC1.U2_RX9P, U2.P2
U2_TX10_N: PIC1.U2_RX10N, U2.R3
U2_TX10_P: PIC1.U2_RX10P, U2.R2
U2_TX11_N: PIC1.U2_RX11N, U2.T3
U2_TX11_P: PIC1.U2_RX11P, U2.T2
U2_TX12_N: PIC1.U2_RX12N, U2.U3
U2_TX12_P: PIC1.U2_RX12P, U2.U2
U2_TX13_N: PIC1.U2_RX13N, U2.V3
U2_TX13_P: PIC1.U2_RX13P, U2.V2
U2_TX14_N: PIC1.U2_RX14N, U2.W3
U2_TX14_P: PIC1.U2_RX14P, U2.W2
U2_TX15_N: PIC1.U2_RX15N, U2.Y3
U2_TX15_P: PIC1.U2_RX15P, U2.Y2
VDD: MA00.VDD, MA00.VDDQ, MA01.VDD, MA01.VDDQ, MA10.VDD, MA10.VDDQ, MA11.VDD, MA11.VDDQ, MB00.VDD, MB00.VDDQ, MB01.VDD, MB01.VDDQ, MB10.VDD, MB10.VDDQ, MB11.VDD, MB11.VDDQ, U1.AA3, U1.AA5, U1.AA7, U1.AA9, U1.AA11, U1.AA13, U1.AA15, U1.AA17, U1.AA19, U1.AA21, U1.AA23, U1.AA25, U1.AA27, U1.AA29, U1.AA31, U1.AA33, U1.AA35, U1.AA37, U1.AA39, U1.AA41, U1.AA43, U1.AA45, U1.AA47, U1.AB4, U1.AB6, U1.AB8, U1.AB10, U1.AB12, U1.AB14, U1.AB16, U1.AB18, U1.AB20, U1.AB22, U1.AB24, U1.AB26, U1.AB28, U1.AB30, U1.AB32, U1.AB34, U1.AB36, U1.AB38, U1.AB40, U1.AB42, U1.AB44, U1.AB46, U1.AC3, U1.AC5, U1.AC7, U1.AC9, U1.AC11, U1.AC13, U1.AC15, U1.AC17, U1.AC19, U1.AC21, U1.AC23, U1.AC25, U1.AC27, U1.AC29, U1.AC31, U1.AC33, U1.AC35, U1.AC37, U1.AC39, U1.AC41, U1.AC43, U1.AC45, U1.AC47, U1.AD4, U1.AD6, U1.AD8, U1.AD10, U1.AD12, U1.AD14, U1.AD16, U1.AD18, U1.AD20, U1.AD22, U1.AD24, U1.AD26, U1.AD28, U1.AD30, U1.AD32, U1.AD34, U1.AD36, U1.AD38, U1.AD40, U1.AD42, U1.AD44, U1.AD46, U1.AE3, U1.AE5, U1.AE7, U1.AE9, U1.AE11, U1.AE13, U1.AE15, U1.AE17, U1.AE19, U1.AE21, U1.AE23, U1.AE25, U1.AE27, U1.AE29, U1.AE31, U1.AE33, U1.AE35, U1.AE37, U1.AE39, U1.AE41, U1.AE43, U1.AE45, U1.AE47, U1.AF4, U1.AF6, U1.AF8, U1.AF10, U1.AF12, U1.AF14, U1.AF16, U1.AF18, U1.AF20, U1.AF22, U1.AF24, U1.AF26, U1.AF28, U1.AF30, U1.AF32, U1.AF34, U1.AF36, U1.AF38, U1.AF40, U1.AF42, U1.AF44, U1.AF46, U1.AG3, U1.AG5, U1.AG7, U1.AG9, U1.AG11, U1.AG13, U1.AG15, U1.AG17, U1.AG19, U1.AG21, U1.AG23, U1.AG25, U1.AG27, U1.AG29, U1.AG31, U1.AG33, U1.AG35, U1.AG37, U1.AG39, U1.AG41, U1.AG43, U1.AG45, U1.AG47, U1.AH4, U1.AH6, U1.AH8, U1.AH10, U1.AH12, U1.AH14, U1.AH16, U1.AH18, U1.AH20, U1.AH22, U1.AH24, U1.AH26, U1.AH28, U1.AH30, U1.AH32, U1.AH34, U1.AH36, U1.AH38, U1.AH40, U1.AH42, U1.AH44, U1.AH46, U1.AJ3, U1.AJ5, U1.AJ7, U1.AJ9, U1.AJ11, U1.AJ13, U1.AJ15, U1.AJ17, U1.AJ19, U1.AJ21, U1.AJ23, U1.AJ25, U1.AJ27, U1.AJ29, U1.AJ31, U1.AJ33, U1.AJ35, U1.AJ37, U1.AJ39, U1.AJ41, U1.AJ43, U1.AJ45, U1.AJ47, U1.AK4, U1.AK6, U1.AK8, U1.AK10, U1.AK12, U1.AK14, U1.AK16, U1.AK18, U1.AK20, U1.AK22, U1.AK24, U1.AK26, U1.AK28, U1.AK30, U1.AK32, U1.AK34, U1.AK36, U1.AK38, U1.AK40, U1.AK42, U1.AK44, U1.AK46, U1.AL3, U1.AL5, U1.AL7, U1.AL9, U1.AL11, U1.AL13, U1.AL15, U1.AL17, U1.AL19, U1.AL21, U1.AL23, U1.AL25, U1.AL27, U1.AL29, U1.AL31, U1.AL33, U1.AL35, U1.AL37, U1.AL39, U1.AL41, U1.AL43, U1.AL45, U1.AL47, U1.AM4, U1.AM6, U1.AM8, U1.AM10, U1.AM12, U1.AM14, U1.AM16, U1.AM18, U1.AM20, U1.AM22, U1.AM24, U1.AM26, U1.AM28, U1.AM30, U1.AM32, U1.AM34, U1.AM36, U1.AM38, U1.AM40, U1.AM42, U1.AM44, U1.AM46, U1.AN3, U1.AN5, U1.AN7, U1.AN9, U1.AN11, U1.AN13, U1.AN15, U1.AN17, U1.AN19, U1.AN21, U1.AN23, U1.AN25, U1.AN27, U1.AN29, U1.AN31, U1.AN33, U1.AN35, U1.AN37, U1.AN39, U1.AN41, U1.AN43, U1.AN45, U1.AN47, U1.AP4, U1.AP6, U1.AP8, U1.AP10, U1.AP12, U1.AP14, U1.AP16, U1.AP18, U1.AP20, U1.AP22, U1.AP24, U1.AP26, U1.AP28, U1.AP30, U1.AP32, U1.AP34, U1.AP36, U1.AP38, U1.AP40, U1.AP42, U1.AP44, U1.AP46, U1.AR3, U1.AR5, U1.AR7, U1.AR9, U1.AR11, U1.AR13, U1.AR15, U1.AR17, U1.AR19, U1.AR21, U1.AR23, U1.AR25, U1.AR27, U1.AR29, U1.AR31, U1.AR33, U1.AR35, U1.AR37, U1.AR39, U1.AR41, U1.AR43, U1.AR45, U1.AR47, U1.AT4, U1.AT6, U1.AT8, U1.AT10, U1.AT12, U1.AT14, U1.AT16, U1.AT18, U1.AT20, U1.AT22, U1.AT24, U1.AT26, U1.AT28, U1.AT30, U1.AT32, U1.AT34, U1.AT36, U1.AT38, U1.AT40, U1.AT42, U1.AT44, U1.AT46, U1.AU3, U1.AU5, U1.AU7, U1.AU9, U1.AU11, U1.AU13, U1.AU15, U1.AU17, U1.AU19, U1.AU21, U1.AU23, U1.AU25, U1.AU27, U1.AU29, U1.AU31, U1.AU33, U1.AU35, U1.AU37, U1.AU39, U1.AU41, U1.AU43, U1.AU45, U1.AU47, U1.AV4, U1.AV6, U1.AV8, U1.AV10, U1.AV12, U1.AV14, U1.AV16, U1.AV18, U1.AV20, U1.AV22, U1.AV24, U1.AV26, U1.AV28, U1.AV30, U1.AV32, U1.AV34, U1.AV36, U1.AV38, U1.AV40, U1.AV42, U1.AV44, U1.AV46, U1.AV48, U1.AW3, U1.AW5, U1.AW7, U1.AW9, U1.AW11, U1.AW13, U1.AW15, U1.AW17, U1.AW19, U1.AW21, U1.AW23, U1.AW25, U1.AW27, U1.AW29, U1.AW31, U1.AW33, U1.AW35, U1.AW37, U1.AW39, U1.AW41, U1.AW43, U1.AW45, U1.AW47, U1.AY4, U1.AY6, U1.AY8, U1.AY10, U1.AY12, U1.AY14, U1.AY16, U1.AY18, U1.AY20, U1.AY22, U1.AY24, U1.AY26, U1.AY28, U1.AY30, U1.AY32, U1.AY34, U1.AY36, U1.AY38, U1.AY40, U1.AY42, U1.AY44, U1.AY46, U1.AY48, U1.BA3, U1.BA5, U1.BA7, U1.BA9, U1.BA11, U1.BA13, U1.BA15, U1.BA17, U1.BA19, U1.BA21, U1.BA23, U1.BA25, U1.BA27, U1.BA29, U1.BA31, U1.BA33, U1.BA35, U1.BA37, U1.BA39, U1.BA41, U1.BA43, U1.BA45, U1.BA47, U1.BB4, U1.BB6, U1.BB8, U1.BB10, U1.BB12, U1.BB14, U1.BB16, U1.BB18, U1.BB20, U1.BB22, U1.BB24, U1.BB26, U1.BB28, U1.BB30, U1.BB32, U1.BB34, U1.BB36, U1.BB38, U1.BB40, U1.BB42, U1.BB44, U1.BB46, U1.BB48, U1.BC3, U1.BC5, U1.BC7, U1.BC9, U1.BC11, U1.BC13, U1.BC15, U1.BC17, U1.BC19, U1.BC21, U1.BC23, U1.BC25, U1.BC27, U1.BC29, U1.BC31, U1.BC33, U1.BC35, U1.BC37, U1.BC39, U1.BC41, U1.BC43, U1.BC45, U1.BC47, U1.BD4, U1.BD6, U1.BD8, U1.BD10, U1.BD12, U1.BD14, U1.BD16, U1.BD18, U1.BD20, U1.BD22, U1.BD24, U1.BD26, U1.BD28, U1.BD30, U1.BD32, U1.BD34, U1.BD36, U1.BD38, U1.BD40, U1.BD42, U1.BD44, U1.BD46, U1.BD48, U1.BE3, U1.BE5, U1.BE7, U1.BE9, U1.BE11, U1.BE13, U1.BE15, U1.BE17, U1.BE19, U1.BE21, U1.BE23, U1.BE25, U1.BE27, U1.BE29, U1.BE31, U1.BE33, U1.BE35, U1.BE37, U1.BE39, U1.BE41, U1.BE43, U1.BE45, U1.BE47, U1.BF4, U1.BF6, U1.BF8, U1.BF10, U1.BF12, U1.BF14, U1.BF16, U1.BF18, U1.BF20, U1.BF22, U1.BF24, U1.BF26, U1.BF28, U1.BF30, U1.BF32, U1.BF34, U1.BF36, U1.BF38, U1.BF40, U1.BF42, U1.BF44, U1.BF46, U1.BF48, U1.BG3, U1.BG5, U1.BG7, U1.BG9, U1.BG11, U1.BG13, U1.BG15, U1.BG17, U1.BG19, U1.BG21, U1.BG23, U1.BG25, U1.BG27, U1.BG29, U1.BG31, U1.BG33, U1.BG35, U1.BG37, U1.BG39, U1.BG41, U1.BG43, U1.BG45, U1.BG47, U1.BH4, U1.BH6, U1.BH8, U1.BH10, U1.BH12, U1.BH14, U1.BH16, U1.BH18, U1.BH20, U1.BH22, U1.BH24, U1.BH26, U1.BH28, U1.BH30, U1.BH32, U1.BH34, U1.BH36, U1.BH38, U1.BH40, U1.BH42, U1.BH44, U1.BH46, U1.BH48, U1.C3, U1.C5, U1.C7, U1.C9, U1.C11, U1.C13, U1.C15, U1.C17, U1.C19, U1.C21, U1.C23, U1.C25, U1.C27, U1.C29, U1.C31, U1.C33, U1.C35, U1.C37, U1.C39, U1.C41, U1.C43, U1.C45, U1.C47, U1.D4, U1.D6, U1.D8, U1.D10, U1.D12, U1.D14, U1.D16, U1.D18, U1.D20, U1.D22, U1.D24, U1.D26, U1.D28, U1.D30, U1.D32, U1.D34, U1.D36, U1.D38, U1.D40, U1.D42, U1.D44, U1.D46, U1.D48, U1.E3, U1.E5, U1.E7, U1.E9, U1.E11, U1.E13, U1.E15, U1.E17, U1.E19, U1.E21, U1.E23, U1.E25, U1.E27, U1.E29, U1.E31, U1.E33, U1.E35, U1.E37, U1.E39, U1.E41, U1.E43, U1.E45, U1.E47, U1.F4, U1.F6, U1.F8, U1.F10, U1.F12, U1.F14, U1.F16, U1.F18, U1.F20, U1.F22, U1.F24, U1.F26, U1.F28, U1.F30, U1.F32, U1.F34, U1.F36, U1.F38, U1.F40, U1.F42, U1.F44, U1.F46, U1.G3, U1.G5, U1.G7, U1.G9, U1.G11, U1.G13, U1.G15, U1.G17, U1.G19, U1.G21, U1.G23, U1.G25, U1.G27, U1.G29, U1.G31, U1.G33, U1.G35, U1.G37, U1.G39, U1.G41, U1.G43, U1.G45, U1.G47, U1.H4, U1.H6, U1.H8, U1.H10, U1.H12, U1.H14, U1.H16, U1.H18, U1.H20, U1.H22, U1.H24, U1.H26, U1.H28, U1.H30, U1.H32, U1.H34, U1.H36, U1.H38, U1.H40, U1.H42, U1.H44, U1.H46, U1.J3, U1.J5, U1.J7, U1.J9, U1.J11, U1.J13, U1.J15, U1.J17, U1.J19, U1.J21, U1.J23, U1.J25, U1.J27, U1.J29, U1.J31, U1.J33, U1.J35, U1.J37, U1.J39, U1.J41, U1.J43, U1.J45, U1.J47, U1.K4, U1.K6, U1.K8, U1.K10, U1.K12, U1.K14, U1.K16, U1.K18, U1.K20, U1.K22, U1.K24, U1.K26, U1.K28, U1.K30, U1.K32, U1.K34, U1.K36, U1.K38, U1.K40, U1.K42, U1.K44, U1.K46, U1.L3, U1.L5, U1.L7, U1.L9, U1.L11, U1.L13, U1.L15, U1.L17, U1.L19, U1.L21, U1.L23, U1.L25, U1.L27, U1.L29, U1.L31, U1.L33, U1.L35, U1.L37, U1.L39, U1.L41, U1.L43, U1.L45, U1.L47, U1.M4, U1.M6, U1.M8, U1.M10, U1.M12, U1.M14, U1.M16, U1.M18, U1.M20, U1.M22, U1.M24, U1.M26, U1.M28, U1.M30, U1.M32, U1.M34, U1.M36, U1.M38, U1.M40, U1.M42, U1.M44, U1.M46, U1.N3, U1.N5, U1.N7, U1.N9, U1.N11, U1.N13, U1.N15, U1.N17, U1.N19, U1.N21, U1.N23, U1.N25, U1.N27, U1.N29, U1.N31, U1.N33, U1.N35, U1.N37, U1.N39, U1.N41, U1.N43, U1.N45, U1.N47, U1.P4, U1.P6, U1.P8, U1.P10, U1.P12, U1.P14, U1.P16, U1.P18, U1.P20, U1.P22, U1.P24, U1.P26, U1.P28, U1.P30, U1.P32, U1.P34, U1.P36, U1.P38, U1.P40, U1.P42, U1.P44, U1.P46, U1.R3, U1.R5, U1.R7, U1.R9, U1.R11, U1.R13, U1.R15, U1.R17, U1.R19, U1.R21, U1.R23, U1.R25, U1.R27, U1.R29, U1.R31, U1.R33, U1.R35, U1.R37, U1.R39, U1.R41, U1.R43, U1.R45, U1.R47, U1.T4, U1.T6, U1.T8, U1.T10, U1.T12, U1.T14, U1.T16, U1.T18, U1.T20, U1.T22, U1.T24, U1.T26, U1.T28, U1.T30, U1.T32, U1.T34, U1.T36, U1.T38, U1.T40, U1.T42, U1.T44, U1.T46, U1.U3, U1.U5, U1.U7, U1.U9, U1.U11, U1.U13, U1.U15, U1.U17, U1.U19, U1.U21, U1.U23, U1.U25, U1.U27, U1.U29, U1.U31, U1.U33, U1.U35, U1.U37, U1.U39, U1.U41, U1.U43, U1.U45, U1.U47, U1.V4, U1.V6, U1.V8, U1.V10, U1.V12, U1.V14, U1.V16, U1.V18, U1.V20, U1.V22, U1.V24, U1.V26, U1.V28, U1.V30, U1.V32, U1.V34, U1.V36, U1.V38, U1.V40, U1.V42, U1.V44, U1.V46, U1.W3, U1.W5, U1.W7, U1.W9, U1.W11, U1.W13, U1.W15, U1.W17, U1.W19, U1.W21, U1.W23, U1.W25, U1.W27, U1.W29, U1.W31, U1.W33, U1.W35, U1.W37, U1.W39, U1.W41, U1.W43, U1.W45, U1.W47, U1.Y4, U1.Y6, U1.Y8, U1.Y10, U1.Y12, U1.Y14, U1.Y16, U1.Y18, U1.Y20, U1.Y22, U1.Y24, U1.Y26, U1.Y28, U1.Y30, U1.Y32, U1.Y34, U1.Y36, U1.Y38, U1.Y40, U1.Y42, U1.Y44, U1.Y46, U2.AA5, U2.AA7, U2.AA9, U2.AA11, U2.AA13, U2.AA15, U2.AA17, U2.AA19, U2.AA21, U2.AA23, U2.AA25, U2.AA27, U2.AA29, U2.AA31, U2.AA33, U2.AA35, U2.AA37, U2.AA39, U2.AA41, U2.AA43, U2.AA45, U2.AA47, U2.AB4, U2.AB6, U2.AB8, U2.AB10, U2.AB12, U2.AB14, U2.AB16, U2.AB18, U2.AB20, U2.AB22, U2.AB24, U2.AB26, U2.AB28, U2.AB30, U2.AB32, U2.AB34, U2.AB36, U2.AB38, U2.AB40, U2.AB42, U2.AB44, U2.AB46, U2.AB48, U2.AC5, U2.AC7, U2.AC9, U2.AC11, U2.AC13, U2.AC15, U2.AC17, U2.AC19, U2.AC21, U2.AC23, U2.AC25, U2.AC27, U2.AC29, U2.AC31, U2.AC33, U2.AC35, U2.AC37, U2.AC39, U2.AC41, U2.AC43, U2.AC45, U2.AC47, U2.AD4, U2.AD6, U2.AD8, U2.AD10, U2.AD12, U2.AD14, U2.AD16, U2.AD18, U2.AD20, U2.AD22, U2.AD24, U2.AD26, U2.AD28, U2.AD30, U2.AD32, U2.AD34, U2.AD36, U2.AD38, U2.AD40, U2.AD42, U2.AD44, U2.AD46, U2.AD48, U2.AE5, U2.AE7, U2.AE9, U2.AE11, U2.AE13, U2.AE15, U2.AE17, U2.AE19, U2.AE21, U2.AE23, U2.AE25, U2.AE27, U2.AE29, U2.AE31, U2.AE33, U2.AE35, U2.AE37, U2.AE39, U2.AE41, U2.AE43, U2.AE45, U2.AE47, U2.AF4, U2.AF6, U2.AF8, U2.AF10, U2.AF12, U2.AF14, U2.AF16, U2.AF18, U2.AF20, U2.AF22, U2.AF24, U2.AF26, U2.AF28, U2.AF30, U2.AF32, U2.AF34, U2.AF36, U2.AF38, U2.AF40, U2.AF42, U2.AF44, U2.AF46, U2.AF48, U2.AG5, U2.AG7, U2.AG9, U2.AG11, U2.AG13, U2.AG15, U2.AG17, U2.AG19, U2.AG21, U2.AG23, U2.AG25, U2.AG27, U2.AG29, U2.AG31, U2.AG33, U2.AG35, U2.AG37, U2.AG39, U2.AG41, U2.AG43, U2.AG45, U2.AG47, U2.AH4, U2.AH6, U2.AH8, U2.AH10, U2.AH12, U2.AH14, U2.AH16, U2.AH18, U2.AH20, U2.AH22, U2.AH24, U2.AH26, U2.AH28, U2.AH30, U2.AH32, U2.AH34, U2.AH36, U2.AH38, U2.AH40, U2.AH42, U2.AH44, U2.AH46, U2.AH48, U2.AJ5, U2.AJ7, U2.AJ9, U2.AJ11, U2.AJ13, U2.AJ15, U2.AJ17, U2.AJ19, U2.AJ21, U2.AJ23, U2.AJ25, U2.AJ27, U2.AJ29, U2.AJ31, U2.AJ33, U2.AJ35, U2.AJ37, U2.AJ39, U2.AJ41, U2.AJ43, U2.AJ45, U2.AJ47, U2.AK4, U2.AK6, U2.AK8, U2.AK10, U2.AK12, U2.AK14, U2.AK16, U2.AK18, U2.AK20, U2.AK22, U2.AK24, U2.AK26, U2.AK28, U2.AK30, U2.AK32, U2.AK34, U2.AK36, U2.AK38, U2.AK40, U2.AK42, U2.AK44, U2.AK46, U2.AK48, U2.AL5, U2.AL7, U2.AL9, U2.AL11, U2.AL13, U2.AL15, U2.AL17, U2.AL19, U2.AL21, U2.AL23, U2.AL25, U2.AL27, U2.AL29, U2.AL31, U2.AL33, U2.AL35, U2.AL37, U2.AL39, U2.AL41, U2.AL43, U2.AL45, U2.AL47, U2.AM4, U2.AM6, U2.AM8, U2.AM10, U2.AM12, U2.AM14, U2.AM16, U2.AM18, U2.AM20, U2.AM22, U2.AM24, U2.AM26, U2.AM28, U2.AM30, U2.AM32, U2.AM34, U2.AM36, U2.AM38, U2.AM40, U2.AM42, U2.AM44, U2.AM46, U2.AM48, U2.AN5, U2.AN7, U2.AN9, U2.AN11, U2.AN13, U2.AN15, U2.AN17, U2.AN19, U2.AN21, U2.AN23, U2.AN25, U2.AN27, U2.AN29, U2.AN31, U2.AN33, U2.AN35, U2.AN37, U2.AN39, U2.AN41, U2.AN43, U2.AN45, U2.AN47, U2.AP4, U2.AP6, U2.AP8, U2.AP10, U2.AP12, U2.AP14, U2.AP16, U2.AP18, U2.AP20, U2.AP22, U2.AP24, U2.AP26, U2.AP28, U2.AP30, U2.AP32, U2.AP34, U2.AP36, U2.AP38, U2.AP40, U2.AP42, U2.AP44, U2.AP46, U2.AP48, U2.AR5, U2.AR7, U2.AR9, U2.AR11, U2.AR13, U2.AR15, U2.AR17, U2.AR19, U2.AR21, U2.AR23, U2.AR25, U2.AR27, U2.AR29, U2.AR31, U2.AR33, U2.AR35, U2.AR37, U2.AR39, U2.AR41, U2.AR43, U2.AR45, U2.AR47, U2.AT4, U2.AT6, U2.AT8, U2.AT10, U2.AT12, U2.AT14, U2.AT16, U2.AT18, U2.AT20, U2.AT22, U2.AT24, U2.AT26, U2.AT28, U2.AT30, U2.AT32, U2.AT34, U2.AT36, U2.AT38, U2.AT40, U2.AT42, U2.AT44, U2.AT46, U2.AT48, U2.AU3, U2.AU5, U2.AU7, U2.AU9, U2.AU11, U2.AU13, U2.AU15, U2.AU17, U2.AU19, U2.AU21, U2.AU23, U2.AU25, U2.AU27, U2.AU29, U2.AU31, U2.AU33, U2.AU35, U2.AU37, U2.AU39, U2.AU41, U2.AU43, U2.AU45, U2.AU47, U2.AV4, U2.AV6, U2.AV8, U2.AV10, U2.AV12, U2.AV14, U2.AV16, U2.AV18, U2.AV20, U2.AV22, U2.AV24, U2.AV26, U2.AV28, U2.AV30, U2.AV32, U2.AV34, U2.AV36, U2.AV38, U2.AV40, U2.AV42, U2.AV44, U2.AV46, U2.AV48, U2.AW3, U2.AW5, U2.AW7, U2.AW9, U2.AW11, U2.AW13, U2.AW15, U2.AW17, U2.AW19, U2.AW21, U2.AW23, U2.AW25, U2.AW27, U2.AW29, U2.AW31, U2.AW33, U2.AW35, U2.AW37, U2.AW39, U2.AW41, U2.AW43, U2.AW45, U2.AW47, U2.AY4, U2.AY6, U2.AY8, U2.AY10, U2.AY12, U2.AY14, U2.AY16, U2.AY18, U2.AY20, U2.AY22, U2.AY24, U2.AY26, U2.AY28, U2.AY30, U2.AY32, U2.AY34, U2.AY36, U2.AY38, U2.AY40, U2.AY42, U2.AY44, U2.AY46, U2.AY48, U2.BA3, U2.BA5, U2.BA7, U2.BA9, U2.BA11, U2.BA13, U2.BA15, U2.BA17, U2.BA19, U2.BA21, U2.BA23, U2.BA25, U2.BA27, U2.BA29, U2.BA31, U2.BA33, U2.BA35, U2.BA37, U2.BA39, U2.BA41, U2.BA43, U2.BA45, U2.BA47, U2.BB4, U2.BB6, U2.BB8, U2.BB10, U2.BB12, U2.BB14, U2.BB16, U2.BB18, U2.BB20, U2.BB22, U2.BB24, U2.BB26, U2.BB28, U2.BB30, U2.BB32, U2.BB34, U2.BB36, U2.BB38, U2.BB40, U2.BB42, U2.BB44, U2.BB46, U2.BB48, U2.BC3, U2.BC5, U2.BC7, U2.BC9, U2.BC11, U2.BC13, U2.BC15, U2.BC17, U2.BC19, U2.BC21, U2.BC23, U2.BC25, U2.BC27, U2.BC29, U2.BC31, U2.BC33, U2.BC35, U2.BC37, U2.BC39, U2.BC41, U2.BC43, U2.BC45, U2.BC47, U2.BD4, U2.BD6, U2.BD8, U2.BD10, U2.BD12, U2.BD14, U2.BD16, U2.BD18, U2.BD20, U2.BD22, U2.BD24, U2.BD26, U2.BD28, U2.BD30, U2.BD32, U2.BD34, U2.BD36, U2.BD38, U2.BD40, U2.BD42, U2.BD44, U2.BD46, U2.BD48, U2.BE3, U2.BE5, U2.BE7, U2.BE9, U2.BE11, U2.BE13, U2.BE15, U2.BE17, U2.BE19, U2.BE21, U2.BE23, U2.BE25, U2.BE27, U2.BE29, U2.BE31, U2.BE33, U2.BE35, U2.BE37, U2.BE39, U2.BE41, U2.BE43, U2.BE45, U2.BE47, U2.BF4, U2.BF6, U2.BF8, U2.BF10, U2.BF12, U2.BF14, U2.BF16, U2.BF18, U2.BF20, U2.BF22, U2.BF24, U2.BF26, U2.BF28, U2.BF30, U2.BF32, U2.BF34, U2.BF36, U2.BF38, U2.BF40, U2.BF42, U2.BF44, U2.BF46, U2.BF48, U2.BG3, U2.BG5, U2.BG7, U2.BG9, U2.BG11, U2.BG13, U2.BG15, U2.BG17, U2.BG19, U2.BG21, U2.BG23, U2.BG25, U2.BG27, U2.BG29, U2.BG31, U2.BG33, U2.BG35, U2.BG37, U2.BG39, U2.BG41, U2.BG43, U2.BG45, U2.BG47, U2.BH4, U2.BH6, U2.BH8, U2.BH10, U2.BH12, U2.BH14, U2.BH16, U2.BH18, U2.BH20, U2.BH22, U2.BH24, U2.BH26, U2.BH28, U2.BH30, U2.BH32, U2.BH34, U2.BH36, U2.BH38, U2.BH40, U2.BH42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
VIN: U100.VIN, U101.VIN, U102.VIN, U103.VIN, U104.VIN, U105.VIN, U106.VIN, U107.VIN, U108.VIN, U109.VIN, U110.VIN, U111.VIN, U112.VIN, U113.VIN, U114.VIN, U115.VIN, U116.VIN, U117.VIN, U118.VIN, U119.VIN, U120.VIN, U121.VIN, U122.VIN, U123.VIN, U124.VIN, U125.VIN, U126.VIN, U127.VIN, U128.VIN, U129.VIN, U130.VIN, U131.VIN, U132.VIN, U133.VIN, U134.VIN, U135.VIN, U136.VIN, U137.VIN, U138.VIN, U139.VIN, U140.VIN, U141.VIN, U142.VIN, U143.VIN, U144.VIN, U145.VIN, U146.VIN, U147.VIN
